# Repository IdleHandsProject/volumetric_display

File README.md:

# TENEX - Open Source Volumetric OLED Display

## Check out the video! - Click the Image

Control up to ten transparent OLED displays using your favourite Feather board.

Find the BOM here: https://www.findchips.com/org/10-open-hardware/list/208915-tenex-project

Shield: [![CC BY-SA 4.0][cc-by-sa-shield]][cc-by-sa]

This work is licensed under a
[Creative Commons Attribution-ShareAlike 4.0 International License][cc-by-sa].

[![CC BY-SA 4.0][cc-by-sa-image]][cc-by-sa]

[cc-by-sa]: http://creativecommons.org/licenses/by-sa/4.0/
[cc-by-sa-image]: https://licensebuttons.net/l/by-sa/4.0/88x31.png
[cc-by-sa-shield]: https://img.shields.io/badge/License-CC%20BY--SA%204.0-lightgrey.svg

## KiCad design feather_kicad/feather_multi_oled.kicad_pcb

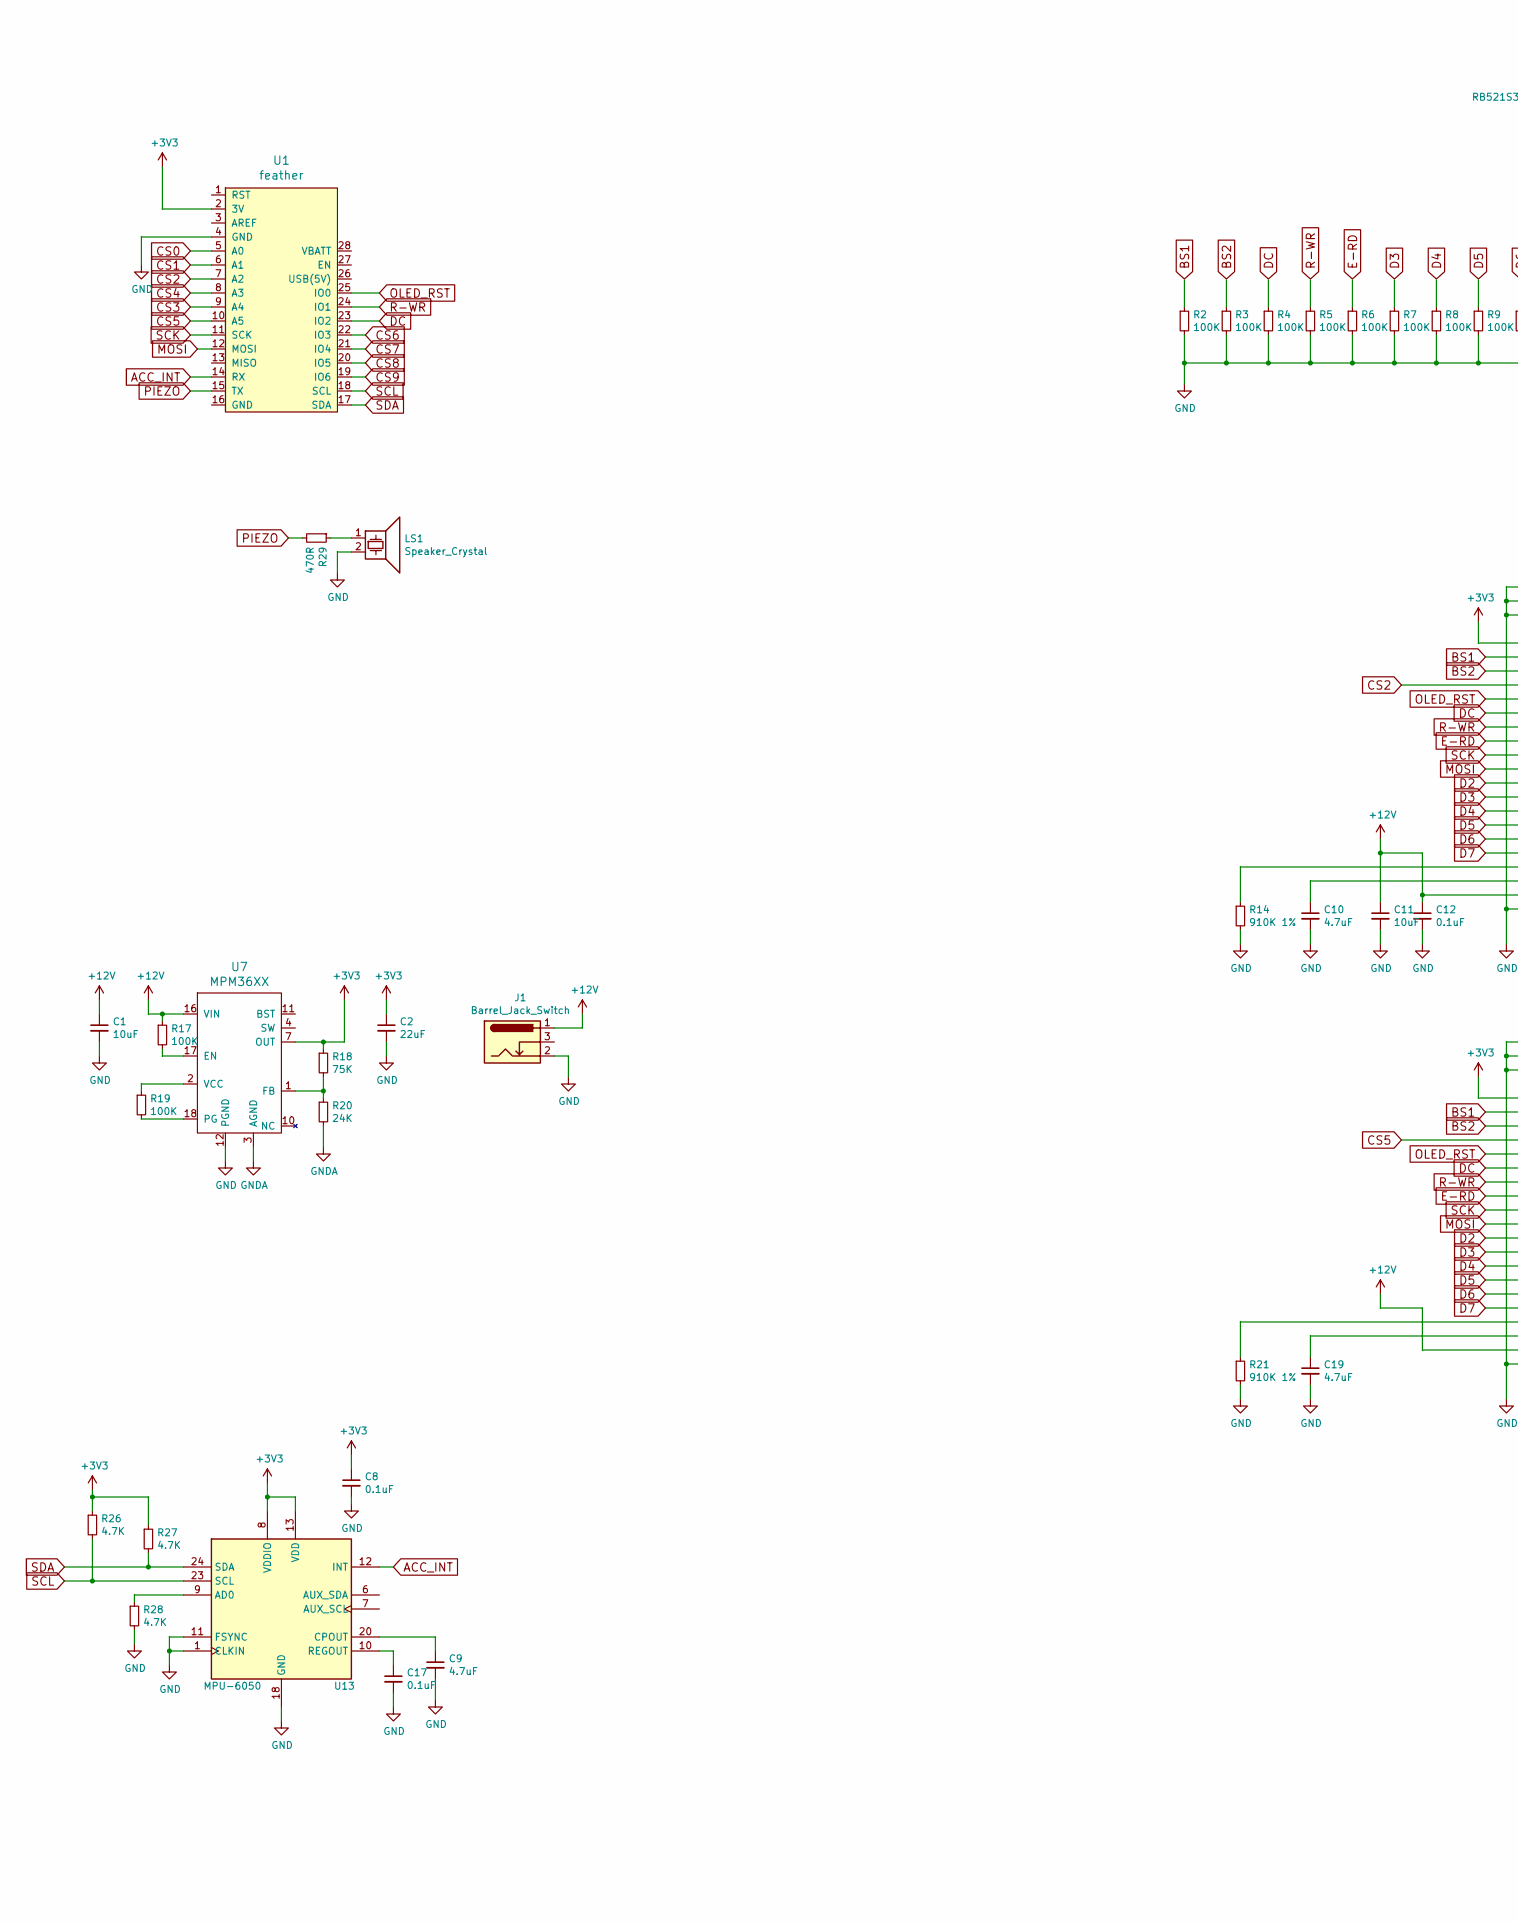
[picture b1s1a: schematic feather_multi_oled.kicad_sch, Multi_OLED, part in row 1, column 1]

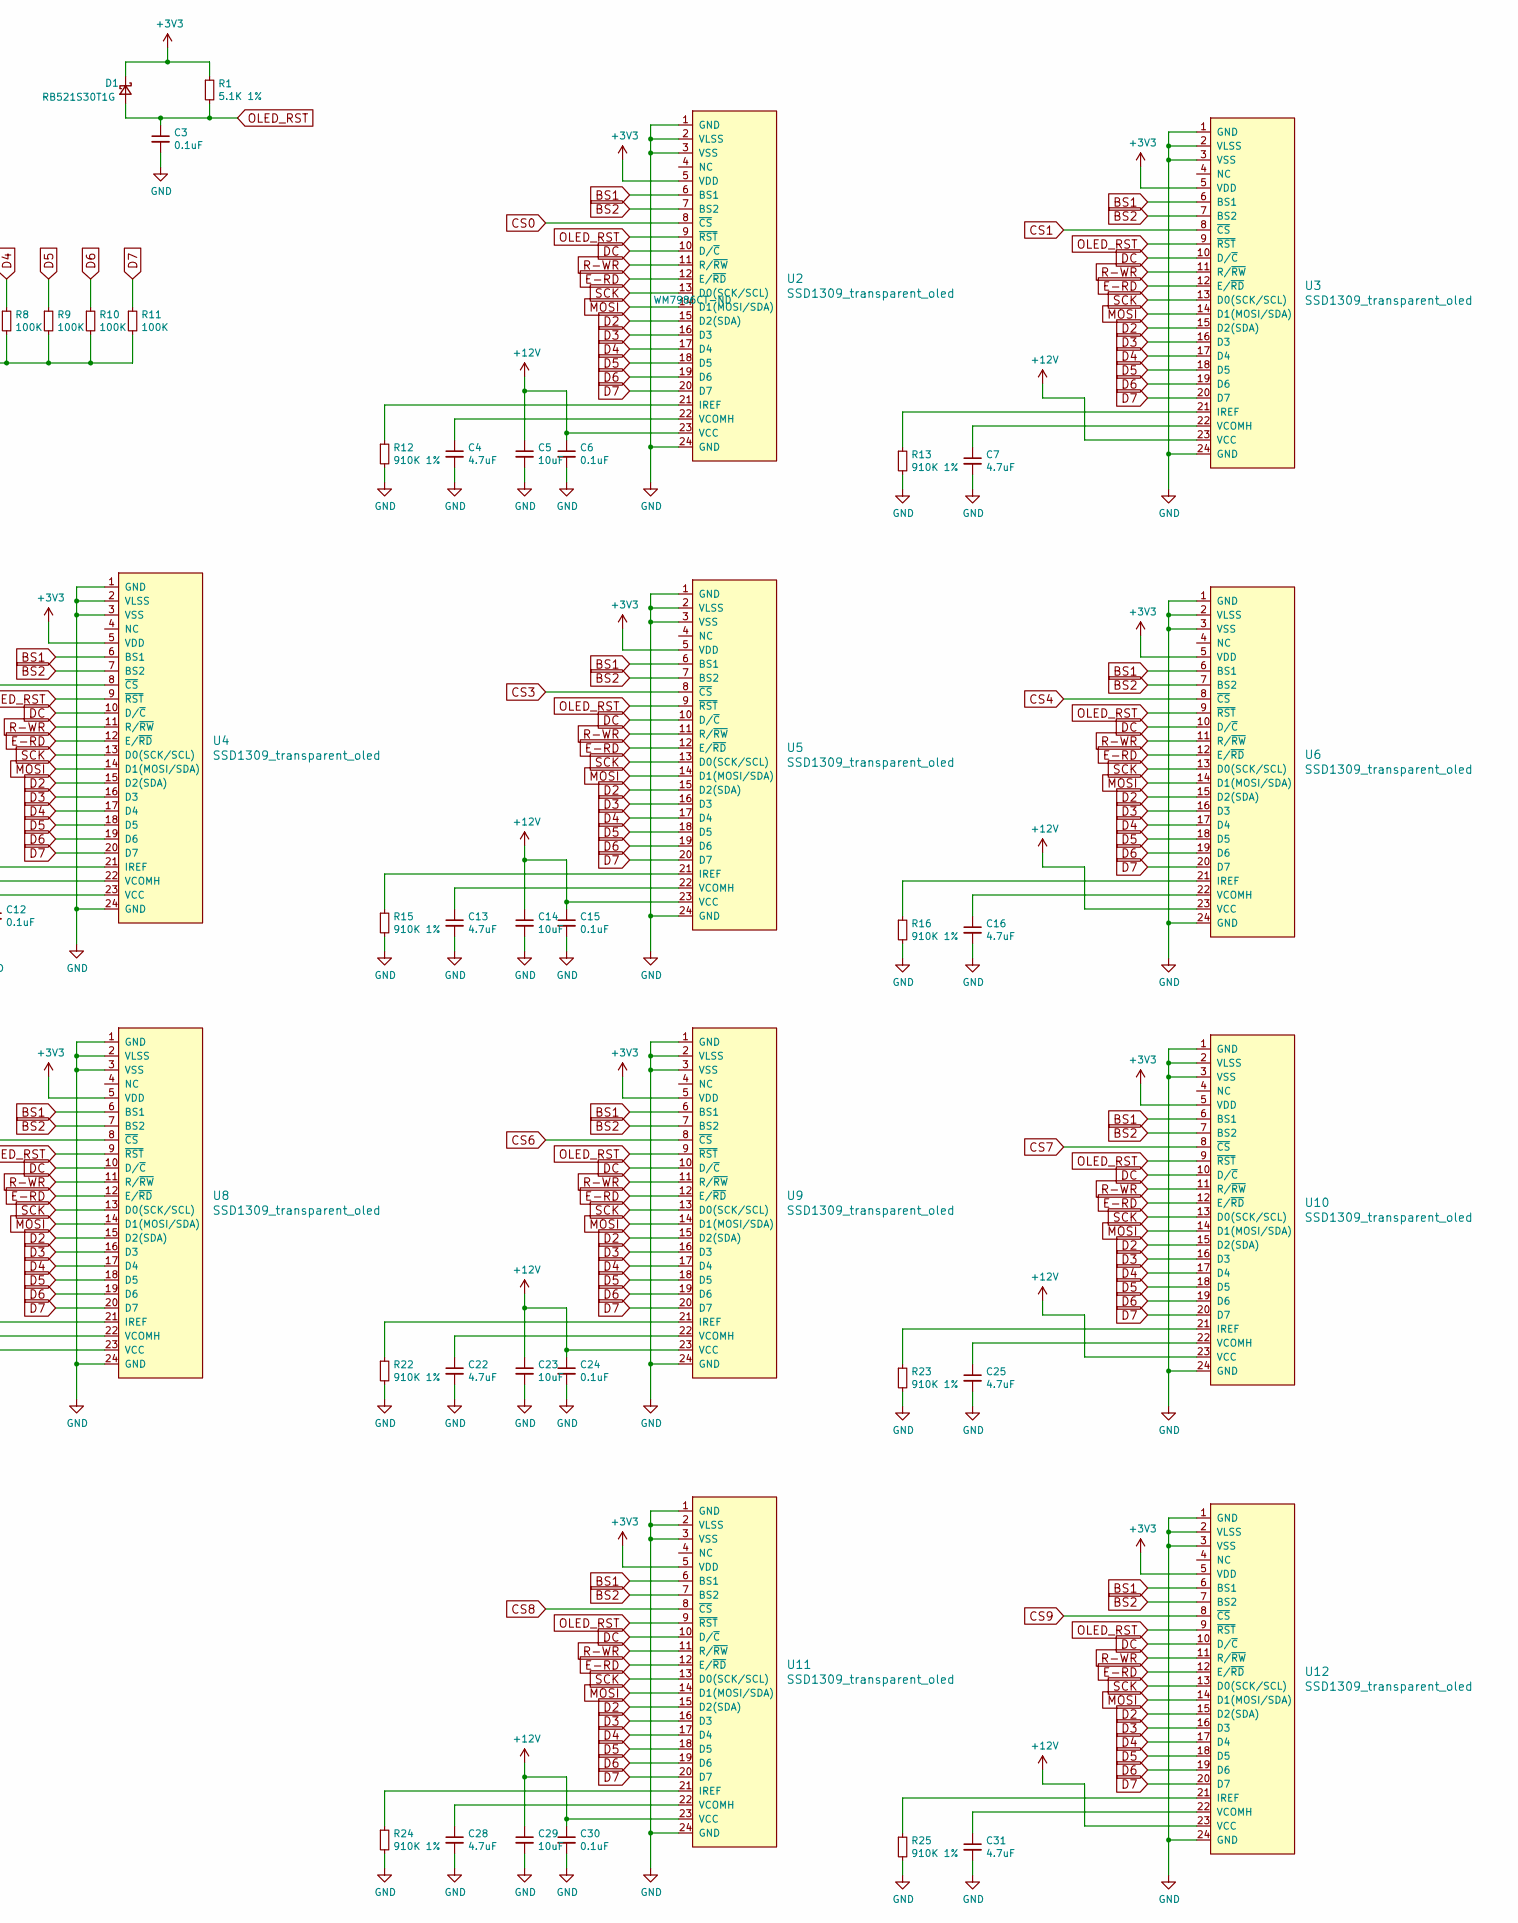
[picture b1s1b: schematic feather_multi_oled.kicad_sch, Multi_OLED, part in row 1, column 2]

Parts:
C1, C5, C11, C14, C23, C29: 10uF; C_0805_2012Metric; Digikey Part No. 311-1869-1-ND
C2: 22uF; C_0805_2012Metric; Digikey Part No. 311-1464-1-ND
C3, C6, C8, C12, C15, C17, C24, C30: 0.1uF; C_0805_2012Metric; Digikey Part No. 311-4348-1-ND
C4, C7, C9, C10, C13, C16, C19, C22, C25, C28, C31: 4.7uF; C_0805_2012Metric; Digikey Part No. 311-3509-2-ND
D1: RB521S30T1G; D_SOD-523; Digikey Part No. NSVRB521S30T1GOSCT-ND
J1: Barrel_Jack_Switch; BarrelJack_Wuerth_6941xx301002; Digikey Part No. 732-5930-ND
LS1: Speaker_Crystal; Buzzer_TDK_PS1240P02BT_D12.2mm_H6.5mm; Digikey Part No. 445-2525-1-ND
R1: 5.1K 1%; R_0805_2012Metric; Digikey Part No. 311-5.10KCRCT-ND
R2, R3, R4, R5, R6, R7, R8, R9, R10, R11, R17, R19: 100K; R_0805_2012Metric; Digikey Part No. RMCF0805FG100KCT-ND
R12, R13, R14, R15, R16, R21, R22, R23, R24, R25: 910K 1%; R_0805_2012Metric; Digikey Part No. YAG3336CT-ND
R18: 75K; R_0805_2012Metric; Digikey Part No. 13-RT0805FRE0775KLCT-ND
R20: 24K; R_0805_2012Metric; Digikey Part No. 13-AC0805FR-0724KLCT-ND
R26, R27, R28: 4.7K; R_0805_2012Metric; Digikey Part No. YAG3364CT-ND
R29: 470R; R_0805_2012Metric; Digikey Part No. 311-470ARCT-ND
U1: feather; PCB_FeatherWing; Digikey Part No. 1528-2648-ND
U2, U3, U4, U5, U6, U8, U9, U10, U11, U12: SSD1309_transparent_oled; FCI_62674-241121ALF; Digikey Part No. WM7986CT-ND
U7: MPM36XX; MPM3606AGQV-Z; Digikey Part No. 1589-1247-1-ND
U13: MPU-6050; InvenSense_QFN-24_4x4mm_P0.5mm; Digikey Part No. 1428-1007-1-ND

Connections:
+3V3: C2.1, C8.1, D1.1 (K), R1.1, R18.1, R26.1, R27.1, U1.2 (3V), U2.5 (VDD), U3.5 (VDD), U4.5 (VDD), U5.5 (VDD), U6.5 (VDD), U7.7 (OUT), U8.5 (VDD), U9.5 (VDD), U10.5 (VDD), U11.5 (VDD), U12.5 (VDD), U13.8 (VDDIO), U13.13 (VDD)
+12V: C1.1, C5.1, C6.1, C11.1, C12.1, C14.1, C15.1, C23.1, C24.1, C29.1, C30.1, J1.1, R17.1, U2.23 (VCC), U3.23 (VCC), U4.23 (VCC), U5.23 (VCC), U6.23 (VCC), U7.16 (VIN), U8.23 (VCC), U9.23 (VCC), U10.23 (VCC), U11.23 (VCC), U12.23 (VCC)
ACC_INT: U1.14 (RX), U13.12 (INT)
BS1: R2.1, U2.6 (BS1), U3.6 (BS1), U4.6 (BS1), U5.6 (BS1), U6.6 (BS1), U8.6 (BS1), U9.6 (BS1), U10.6 (BS1), U11.6 (BS1), U12.6 (BS1)
BS2: R3.1, U2.7 (BS2), U3.7 (BS2), U4.7 (BS2), U5.7 (BS2), U6.7 (BS2), U8.7 (BS2), U9.7 (BS2), U10.7 (BS2), U11.7 (BS2), U12.7 (BS2)
CS0: U1.5 (A0), U2.8 (~CS)
CS1: U1.6 (A1), U3.8 (~CS)
CS2: U1.7 (A2), U4.8 (~CS)
CS3: U1.9 (A4), U5.8 (~CS)
CS4: U1.8 (A3), U6.8 (~CS)
CS5: U1.10 (A5), U8.8 (~CS)
CS6: U1.22 (IO3), U9.8 (~CS)
CS7: U1.21 (IO4), U10.8 (~CS)
CS8: U1.20 (IO5), U11.8 (~CS)
CS9: U1.19 (IO6), U12.8 (~CS)
D2: U2.15 (D2(SDA)), U3.15 (D2(SDA)), U4.15 (D2(SDA)), U5.15 (D2(SDA)), U6.15 (D2(SDA)), U8.15 (D2(SDA)), U9.15 (D2(SDA)), U10.15 (D2(SDA)), U11.15 (D2(SDA)), U12.15 (D2(SDA))
D3: R7.1, U2.16 (D3), U3.16 (D3), U4.16 (D3), U5.16 (D3), U6.16 (D3), U8.16 (D3), U9.16 (D3), U10.16 (D3), U11.16 (D3), U12.16 (D3)
D4: R8.1, U2.17 (D4), U3.17 (D4), U4.17 (D4), U5.17 (D4), U6.17 (D4), U8.17 (D4), U9.17 (D4), U10.17 (D4), U11.17 (D4), U12.17 (D4)
D5: R9.1, U2.18 (D5), U3.18 (D5), U4.18 (D5), U5.18 (D5), U6.18 (D5), U8.18 (D5), U9.18 (D5), U10.18 (D5), U11.18 (D5), U12.18 (D5)
D6: R10.1, U2.19 (D6), U3.19 (D6), U4.19 (D6), U5.19 (D6), U6.19 (D6), U8.19 (D6), U9.19 (D6), U10.19 (D6), U11.19 (D6), U12.19 (D6)
D7: R11.1, U2.20 (D7), U3.20 (D7), U4.20 (D7), U5.20 (D7), U6.20 (D7), U8.20 (D7), U9.20 (D7), U10.20 (D7), U11.20 (D7), U12.20 (D7)
DC: R4.1, U1.23 (IO2), U2.10 (D/~C), U3.10 (D/~C), U4.10 (D/~C), U5.10 (D/~C), U6.10 (D/~C), U8.10 (D/~C), U9.10 (D/~C), U10.10 (D/~C), U11.10 (D/~C), U12.10 (D/~C)
E-RD: R6.1, U2.12 (E/~RD), U3.12 (E/~RD), U4.12 (E/~RD), U5.12 (E/~RD), U6.12 (E/~RD), U8.12 (E/~RD), U9.12 (E/~RD), U10.12 (E/~RD), U11.12 (E/~RD), U12.12 (E/~RD)
GND: C1.2, C2.2, C3.2, C4.2, C5.2, C6.2, C7.2, C8.2, C9.2, C10.2, C11.2, C12.2, C13.2, C14.2, C15.2, C16.2, C17.2, C19.2, C22.2, C23.2, C24.2, C25.2, C28.2, C29.2, C30.2, C31.2, J1.2, LS1.2, R2.2, R3.2, R4.2, R5.2, R6.2, R7.2, R8.2, R9.2, R10.2, R11.2, R12.2, R13.2, R14.2, R15.2, R16.2, R21.2, R22.2, R23.2, R24.2, R25.2, R28.2, U1.4 (GND), U2.1 (GND), U2.2 (VLSS), U2.3 (VSS), U2.24 (GND), U3.1 (GND), U3.2 (VLSS), U3.3 (VSS), U3.24 (GND), U4.1 (GND), U4.2 (VLSS), U4.3 (VSS), U4.24 (GND), U5.1 (GND), U5.2 (VLSS), U5.3 (VSS), U5.24 (GND), U6.1 (GND), U6.2 (VLSS), U6.3 (VSS), U6.24 (GND), U7.12 (PGND), U8.1 (GND), U8.2 (VLSS), U8.3 (VSS), U8.24 (GND), U9.1 (GND), U9.2 (VLSS), U9.3 (VSS), U9.24 (GND), U10.1 (GND), U10.2 (VLSS), U10.3 (VSS), U10.24 (GND), U11.1 (GND), U11.2 (VLSS), U11.3 (VSS), U11.24 (GND), U12.1 (GND), U12.2 (VLSS), U12.3 (VSS), U12.24 (GND), U13.1 (CLKIN), U13.11 (FSYNC), U13.18 (GND)
GNDA: R20.2, U7.3 (AGND)
MOSI: U1.12 (MOSI), U2.14 (D1(MOSI/SDA)), U3.14 (D1(MOSI/SDA)), U4.14 (D1(MOSI/SDA)), U5.14 (D1(MOSI/SDA)), U6.14 (D1(MOSI/SDA)), U8.14 (D1(MOSI/SDA)), U9.14 (D1(MOSI/SDA)), U10.14 (D1(MOSI/SDA)), U11.14 (D1(MOSI/SDA)), U12.14 (D1(MOSI/SDA))
unnamed: C4.1, U2.22 (VCOMH)
unnamed: C7.1, U3.22 (VCOMH)
unnamed: C9.1, U13.20 (CPOUT)
unnamed: C10.1, U4.22 (VCOMH)
unnamed: C13.1, U5.22 (VCOMH)
unnamed: C16.1, U6.22 (VCOMH)
unnamed: C17.1, U13.10 (REGOUT)
unnamed: C19.1, U8.22 (VCOMH)
unnamed: C22.1, U9.22 (VCOMH)
unnamed: C25.1, U10.22 (VCOMH)
unnamed: C28.1, U11.22 (VCOMH)
unnamed: C31.1, U12.22 (VCOMH)
unnamed: LS1.1, R29.1
unnamed: R12.1, U2.21 (IREF)
unnamed: R13.1, U3.21 (IREF)
unnamed: R14.1, U4.21 (IREF)
unnamed: R15.1, U5.21 (IREF)
unnamed: R16.1, U6.21 (IREF)
unnamed: R17.2, U7.17 (EN)
unnamed: R18.2, R20.1, U7.1 (FB)
unnamed: R19.1, U7.2 (VCC)
unnamed: R19.2, U7.18 (PG)
unnamed: R21.1, U8.21 (IREF)
unnamed: R22.1, U9.21 (IREF)
unnamed: R23.1, U10.21 (IREF)
unnamed: R24.1, U11.21 (IREF)
unnamed: R25.1, U12.21 (IREF)
unnamed: R28.1, U13.9 (AD0)
OLED_RST: C3.1, D1.2 (A), R1.2, U1.25 (IO0), U2.9 (~RST), U3.9 (~RST), U4.9 (~RST), U5.9 (~RST), U6.9 (~RST), U8.9 (~RST), U9.9 (~RST), U10.9 (~RST), U11.9 (~RST), U12.9 (~RST)
PIEZO: R29.2, U1.15 (TX)
R-WR: R5.1, U1.24 (IO1), U2.11 (R/~RW), U3.11 (R/~RW), U4.11 (R/~RW), U5.11 (R/~RW), U6.11 (R/~RW), U8.11 (R/~RW), U9.11 (R/~RW), U10.11 (R/~RW), U11.11 (R/~RW), U12.11 (R/~RW)
SCK: U1.11 (SCK), U2.13 (D0(SCK/SCL)), U3.13 (D0(SCK/SCL)), U4.13 (D0(SCK/SCL)), U5.13 (D0(SCK/SCL)), U6.13 (D0(SCK/SCL)), U8.13 (D0(SCK/SCL)), U9.13 (D0(SCK/SCL)), U10.13 (D0(SCK/SCL)), U11.13 (D0(SCK/SCL)), U12.13 (D0(SCK/SCL))
SCL: R26.2, U1.18 (SCL), U13.23 (SCL)
SDA: R27.2, U1.17 (SDA), U13.24 (SDA)

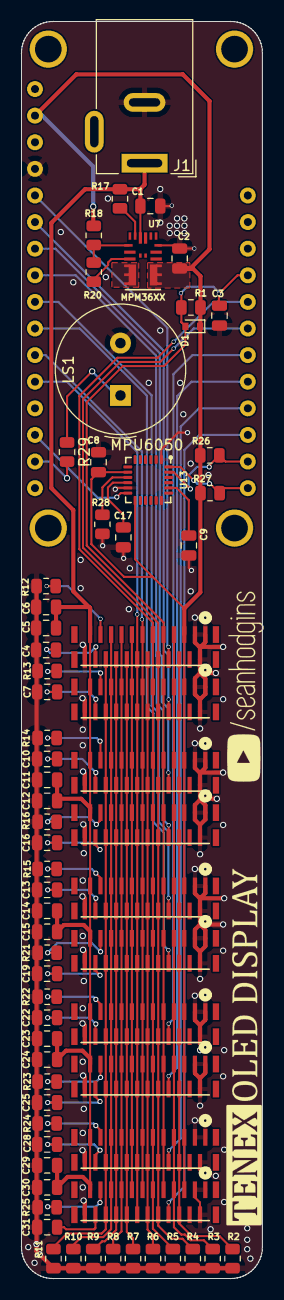
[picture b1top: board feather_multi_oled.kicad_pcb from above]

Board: 2 copper layers, 23.0 x 120.0 mm, 70 parts (0 on the bottom side), 58 nets.

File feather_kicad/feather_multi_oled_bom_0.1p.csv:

Component,Description,Part,References,Value,Footprint,Quantity Per PCB,Datasheet,Digikey Part No.
1,"Unpolarized capacitor, small symbol",C_Small,C3 C6 C8 C12 C15 C17 C24 C30,0.1uF,C_0805_2012Metric,8,~,311-4348-1-ND
2,"Unpolarized capacitor, small symbol",C_Small,C4 C7 C9 C10 C13 C16 C19 C22 C25 C28 C31,4.7uF,C_0805_2012Metric,11,~,311-3509-2-ND
3,"Unpolarized capacitor, small symbol",C_Small,C1 C5 C11 C14 C23 C29,10uF,C_0805_2012Metric,6,~,311-1869-1-ND
4,"Unpolarized capacitor, small symbol",C_Small,C2,22uF,C_0805_2012Metric,1,~,311-1464-1-ND
5,"Schottky diode, small symbol",D_Schottky_Small,D1,RB521S30T1G,D_SOD-523,1,~,NSVRB521S30T1GOSCT-ND
6,DC Barrel Jack with an internal switch,Barrel_Jack_Switch,J1,Barrel_Jack_Switch,BarrelJack_Wuerth_6941xx301002,1,~,732-5930-ND
7,Crystal speaker/transducer,Speaker_Crystal,LS1,Speaker_Crystal,Buzzer_TDK_PS1240P02BT_D12.2mm_H6.5mm,1,~,445-2525-1-ND
8,"Resistor, small symbol",R_Small,R29,470R,R_0805_2012Metric,1,~,311-470ARCT-ND
9,"Resistor, small symbol",R_Small,R26 R27 R28,4.7K,R_0805_2012Metric,3,~,YAG3364CT-ND
10,,R_Small,R20,24K,R_0805_2012Metric,1,,13-AC0805FR-0724KLCT-ND
11,,R_Small,R18,75K,R_0805_2012Metric,1,,13-RT0805FRE0775KLCT-ND
12,"Resistor, small symbol",R_Small,R2 R3 R4 R5 R6 R7 R8 R9 R10 R11,100K,R_0805_2012Metric,10,~,RMCF0805FG100KCT-ND
13,,R_Small,R17 R19,100K,R_0805_2012Metric,2,,RMCF0805FG100KCT-ND
14,"Resistor, small symbol",R_Small,R1,5.1K 1%,R_0805_2012Metric,1,~,311-5.10KCRCT-ND
15,"Resistor, small symbol",R_Small,R12 R13 R14 R15 R16 R21 R22 R23 R24 R25,910K 1%,R_0805_2012Metric,10,~,YAG3336CT-ND
16,,MPM36XX,U7,MPM36XX,MPM3606AGQV-Z,1,https://www.monolithicpower.com/en/documentview/productdocum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,1589-1247-1-ND
17,"InvenSense 6-Axis Motion Sensor, Gyroscope, Accelerometer, I2C",MPU-6050,U13,MPU-6050,InvenSense_QFN-24_4x4mm_P0.5mm,1,https://store.invensense.com/datasheets/invensense/MPU-6050_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,1428-1007-1-ND
18,,SSD1309_transparent_oled,U2 U3 U4 U5 U6 U8 U9 U10 U11 U12,SSD1309_transparent_oled,FCI_62674-241121ALF,10,,609-1210-1-ND
19,,feather,U1,feather,PCB_FeatherWing,1,,1528-2648-ND

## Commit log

2021-03-01 Its OCF
2021-03-01 new file
2021-03-02 before video upload
2021-03-02 Added BOM
2021-03-04 added Display Top and STP
2022-10-21 Updated license to CC
2022-10-21 Create CC License File
2023-11-15 Update ParticlePhysics_2D_MPU.ino
    Simple bit shift left vs a multiplication by 2 when calculating back in the range of random motion.
2024-07-09 updated BOM for new 24 Pin FCP Connector P/N

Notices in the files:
parts and their libraries:
Copyright 2016 Accelerated Designs. All rights reserved.
